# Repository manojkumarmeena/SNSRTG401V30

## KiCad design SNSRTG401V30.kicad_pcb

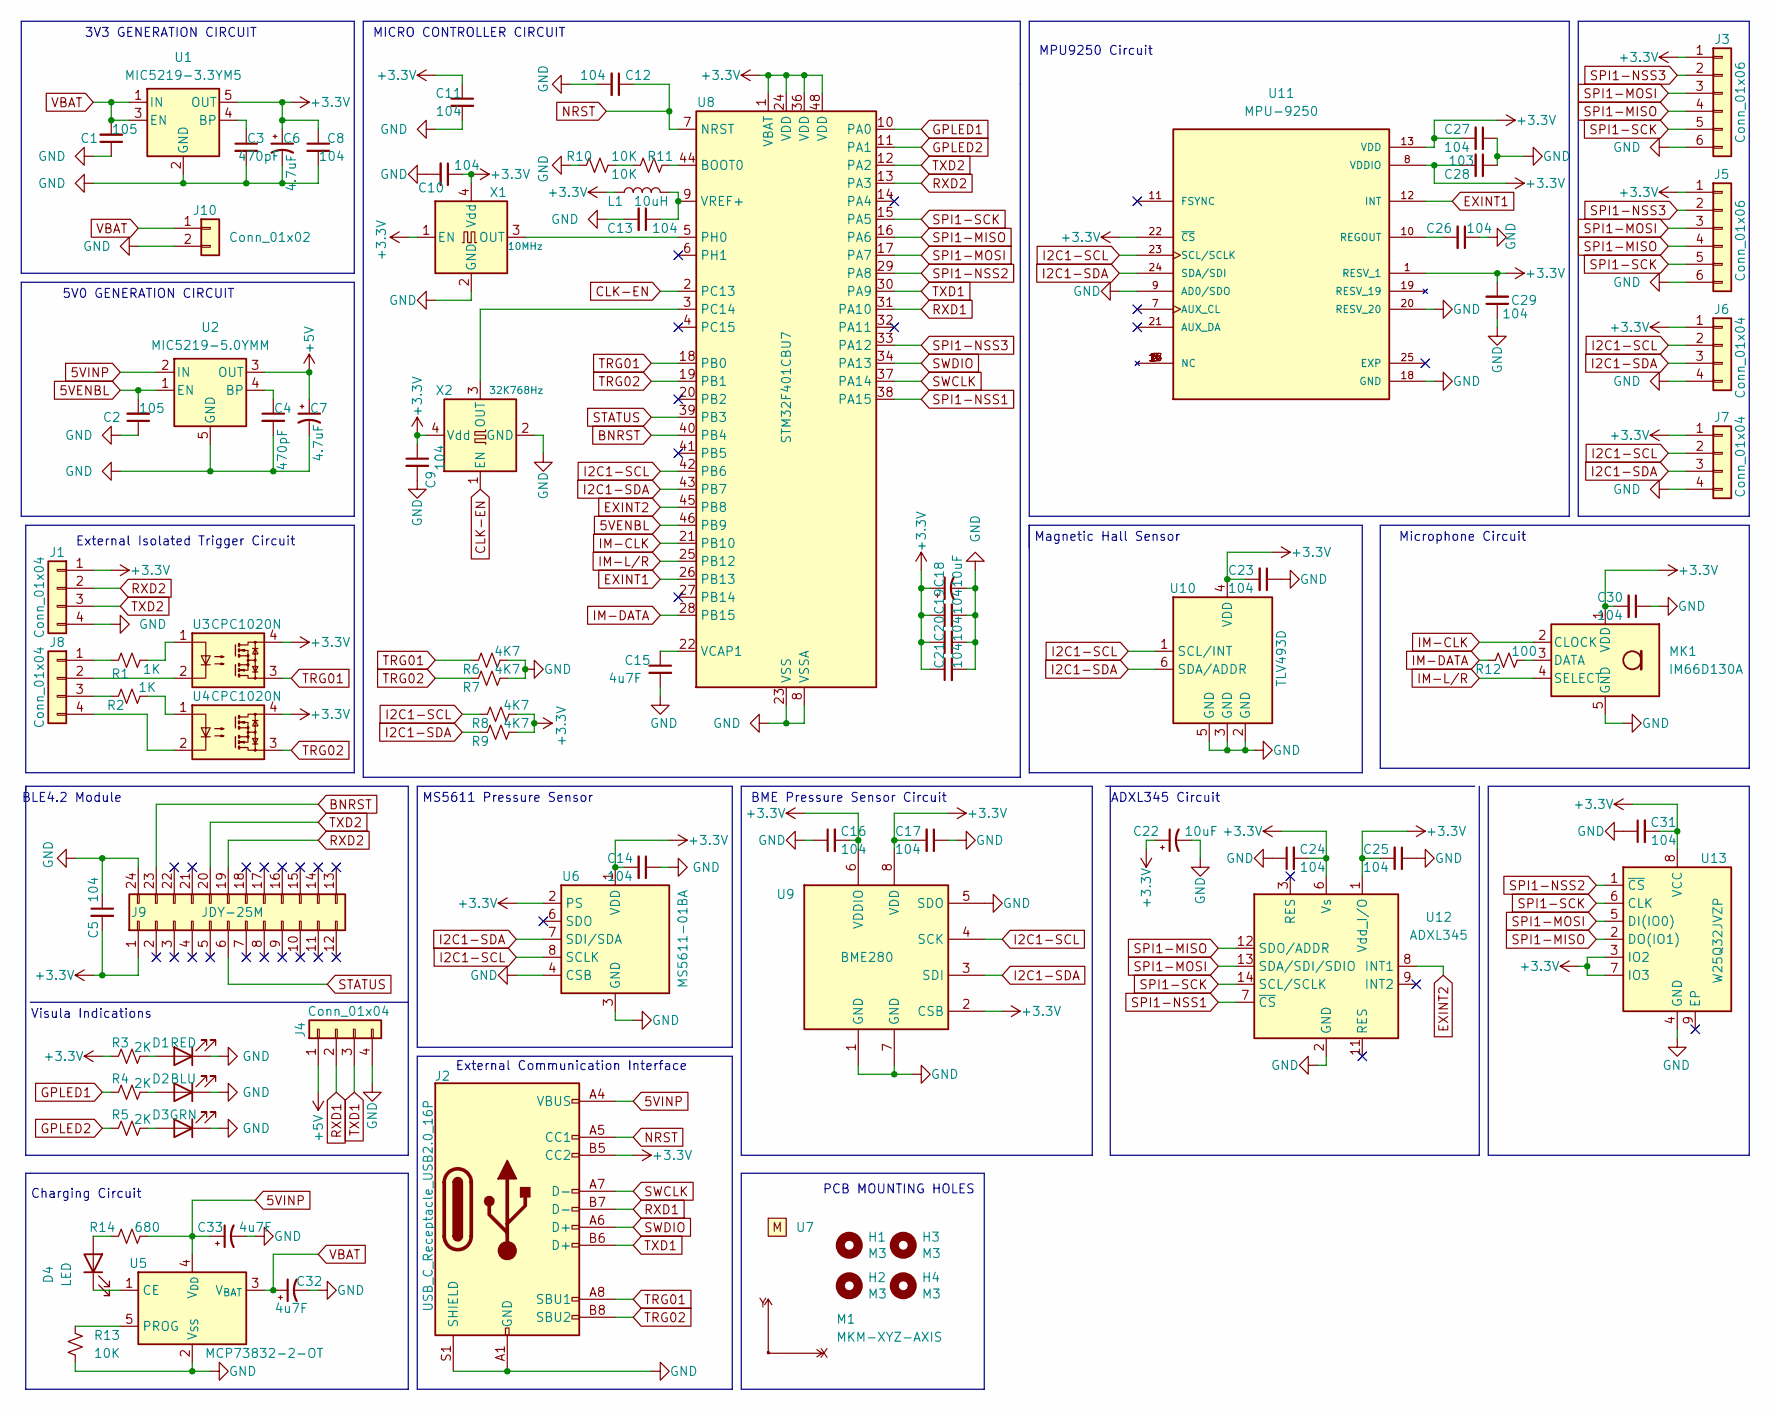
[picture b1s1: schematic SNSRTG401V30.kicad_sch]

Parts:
C1, C2: 105; C_0805_2012Metric_Pad1.18x1.45mm_HandSolder; PartNo C0805C105K4RACAUTO
C3, C4: 470pF; C_0603_1608Metric_Pad1.08x0.95mm_HandSolder; PartNo C0603C471J5GACAUTO
C5, C8, C9, C10, C11, C12, C13, C14, C16, C17, C19, C20, C21, C23, C24, C25, C26, C27, C29, C30, C31: 104; C_0603_1608Metric_Pad1.08x0.95mm_HandSolder; PartNo C0603C104J5RACAUTO
C6, C7: 4.7uF; CP_EIA-3216-18_Kemet-A; PartNo T491A475K016AT
C15: 4u7F; C_1206_3216Metric_Pad1.33x1.80mm_HandSolder; PartNo C1206C475K5PACTU
C18, C22: 10uF; CP_EIA-3216-18_Kemet-A; PartNo T491A106K016AT
C28: 103; C_0603_1608Metric_Pad1.08x0.95mm_HandSolder; PartNo C0603C103J3GECAUTO
C32, C33: 4u7F; CP_EIA-3216-18_Kemet-A
D1: RED; LED_0603_1608Metric_Pad1.05x0.95mm_HandSolder; PartNo VLMS1300-GS08
D2: BLU; LED_0603_1608Metric_Pad1.05x0.95mm_HandSolder; PartNo VLMB1300-GS08
D3: GRN; LED_0603_1608Metric_Pad1.05x0.95mm_HandSolder; PartNo VLMTG1401-GS08
D4: LED; LED_0603_1608Metric_Pad1.05x0.95mm_HandSolder
H1, H2, H3, H4: M3; MountingHole_3.2mm_M3
J1, J4, J6, J8: Conn_01x04; PinHeader_1x04_P1.27mm_Vertical
J2: USB_C_Receptacle_USB2.0_16P; USB_C_Receptacle_GCT_USB4105-xx-A_16P_TopMnt_Horizontal
J3: Conn_01x06; PinHeader_1x06_P1.27mm_Vertical
J5: Conn_01x06; PinHeader_1x06_P1.00mm_Vertical
J7: Conn_01x04; PinHeader_1x04_P1.00mm_Vertical
J9: JDY-25M; JDY-08
J10: Conn_01x02; PinHeader_1x02_P1.27mm_Vertical
L1: 10uH; L_0603_1608Metric_Pad1.05x0.95mm_HandSolder; PartNo FCM1608KF-601T03
M1: MKM-XYZ-AXIS; BullsEye
MK1: IM66D130A; Infineon_PG-LLGA-5-1
R1, R2: 1K; R_0603_1608Metric_Pad0.98x0.95mm_HandSolder; PartNo CRCW06031K00FKEAHP
R3, R4, R5: 2K; R_0603_1608Metric_Pad0.98x0.95mm_HandSolder; PartNo CRCW06032K00FKEAHP
R6, R7, R8, R9: 4K7; R_0603_1608Metric_Pad0.98x0.95mm_HandSolder; PartNo CRCW06034K70FKEAHP
R10, R11: 10K; R_0603_1608Metric_Pad0.98x0.95mm_HandSolder; PartNo CRCW060310K0FKEAHP
R12: 100; R_0603_1608Metric_Pad0.98x0.95mm_HandSolder; PartNo CRCW0603120RFKEAHP
R13: 10K; R_0603_1608Metric_Pad0.98x0.95mm_HandSolder
R14: 680; R_0603_1608Metric_Pad0.98x0.95mm_HandSolder
U1: MIC5219-3.3YM5; SOT-23-5; PartNo MIC5219-3.3YM5-TR
U2: MIC5219-5.0YMM; MSOP-8_3x3mm_P0.65mm; PartNo MIC5219-5.0YMM
U3, U4: CPC1020N; SOP-4_3.8x4.1mm_P2.54mm; PartNo CPC1020N
U5: MCP73832-2-OT; SOT-23-5
U6: MS5611-01BA; LGA-8_3x5mm_P1.25mm; PartNo MS561101BA03-50
U7: MKM-LOGON-V10; MKMLOGO-P
U8: STM32F401CBU7; QFN-48-1EP_7x7mm_P0.5mm_EP5.6x5.6mm; PartNo STM32F401CBU7
U9: BME280; Bosch_LGA-8_2.5x2.5mm_P0.65mm_ClockwisePinNumbering; PartNo BME280
U10: TLV493D; SOT-23-6; PartNo TLV493DA1B6HTSA2
U11: MPU-9250; MPU9250-QFN24-3x3mm-P0.4mm; PartNo MPU-9250
U12: ADXL345; ADXL375-LGA-3x5MM; PartNo ADXL345BCCZ
U13: W25Q32JVZP; WSON-8-1EP_8x6mm_P1.27mm_EP3.4x4.3mm; PartNo W25Q512JVEIQ
X1: 10MHz; Oscillator_SMD_Abracon_ASDMB-4Pin_2.5x2.0mm; PartNo 8NJ-10.000MDE-T
X2: 32K768Hz; Oscillator_SMD_Abracon_ASDMB-4Pin_2.5x2.0mm; PartNo ABS07-120-32.768KHZ-T

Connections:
5VENBL: C2.2, U2.1 (EN), U8.46 (PB9)
5VINP: C33.1, J2.A4 (VBUS), J2.A9 (VBUS), J2.B4 (VBUS), J2.B9 (VBUS), R14.1, U2.2 (IN), U5.4 (V_{DD})
+3.3V: C5.2, C6.1, C8.1, C9.1, C10.1, C11.1, C14.2, C16.2, C17.2, C18.1, C19.1, C20.1, C21.1, C22.1, C23.2, C24.2, C25.2, C27.2, C28.2, C29.2, C30.2, C31.2, J1.1, J2.B5 (CC2), J3.1, J5.1, J6.1, J7.1, J9.1, L1.1, MK1.1 (VDD), R3.1, R8.2, R9.2, U1.5 (OUT), U3.4, U4.4, U6.1 (VDD), U6.2 (PS), U8.1 (VBAT), U8.24 (VDD), U8.36 (VDD), U8.48 (VDD), U9.2 (CSB), U9.6 (VDDIO), U9.8 (VDD), U10.4 (VDD), U11.1 (RESV_1), U11.8 (VDDIO), U11.13 (VDD), U11.22 (~CS), U12.1 (Vdd_I/O), U12.6 (Vs), U13.3 (IO2), U13.7 (IO3), U13.8 (VCC), X1.1 (EN), X1.4 (Vdd), X2.4 (Vdd)
+5V: C7.1, J4.1, U2.3 (OUT)
BNRST: J9.23, U8.40 (PB4)
CLK-EN: U8.2 (PC13), X2.1 (EN)
EXINT1: U8.26 (PB13), U11.12 (INT)
EXINT2: U8.45 (PB8), U12.8 (INT1)
GND: C1.1, C2.1, C3.2, C4.2, C5.1, C6.2, C7.2, C8.2, C9.2, C10.2, C11.2, C12.2, C13.2, C14.1, C15.2, C16.1, C17.1, C18.2, C19.2, C20.2, C21.2, C22.2, C23.1, C24.1, C25.1, C26.1, C27.1, C28.1, C29.1, C30.1, C31.1, C32.2, C33.2, D1.1 (K), D2.1 (K), D3.1 (K), J1.4, J2.A1 (GND), J2.A12 (GND), J2.B1 (GND), J2.B12 (GND), J2.S1 (SHIELD), J3.6, J4.4, J5.6, J6.4, J7.4, J9.24, J10.2, MK1.5 (GND), R6.2, R7.2, R10.1, R13.2, U1.2 (GND), U2.5 (GND), U2.6 (GND), U2.7 (GND), U2.8 (GND), U5.2 (V_{SS}), U6.3 (GND), U6.4 (CSB), U6.5 (CSB), U8.8 (VSSA), U8.23 (VSS), U8.35 (VSS), U8.47 (VSS), U8.49 (VSS), U9.1 (GND), U9.5 (SDO), U9.7 (GND), U10.2 (GND), U10.3 (GND), U10.5 (GND), U11.9 (AD0/SDO), U11.18 (GND), U11.20 (RESV_20), U12.2 (GND), U12.4 (GND), U12.5 (GND), U13.4 (GND), X1.2 (GND), X2.2 (GND)
GPLED1: R4.1, U8.10 (PA0)
GPLED2: R5.1, U8.11 (PA1)
I2C1-SCL: J6.2, J7.2, R8.1, U6.8 (SCLK), U8.42 (PB6), U9.4 (SCK), U10.1 (SCL/INT), U11.23 (SCL/SCLK)
I2C1-SDA: J6.3, J7.3, R9.1, U6.7 (SDI/SDA), U8.43 (PB7), U9.3 (SDI), U10.6 (SDA/ADDR), U11.24 (SDA/SDI)
IM-CLK: MK1.2 (CLOCK), U8.21 (PB10)
IM-DATA: R12.1, U8.28 (PB15)
IM-L/R: MK1.4 (SELECT), U8.25 (PB12)
NRST: C12.1, J2.A5 (CC1), U8.7 (NRST)
unnamed: D1.2 (A), R3.2
unnamed: D2.2 (A), R4.2
unnamed: D3.2 (A), R5.2
unnamed: D4.2 (A), R14.2
unnamed: D4.1 (K), U5.1 (CE)
unnamed: J8.1, R1.1
unnamed: J8.2, U3.2
unnamed: J8.3, R2.1
unnamed: J8.4, U4.2
unnamed: MK1.3 (DATA), R12.2
unnamed: R1.2, U3.1
unnamed: R2.2, U4.1
unnamed: R10.2, R11.1
unnamed: C3.1, U1.4 (BP)
unnamed: C4.1, U2.4 (BP)
unnamed: R13.1, U5.5 (PROG)
unnamed: R11.2, U8.44 (BOOT0)
unnamed: U8.3 (PC14), X2.3 (OUT)
unnamed: U8.5 (PH0), X1.3 (OUT)
unnamed: C15.1, U8.22 (VCAP1)
unnamed: C13.1, L1.2, U8.9 (VREF+)
unnamed: C26.2, U11.10 (REGOUT)
RXD1: J2.B7 (D-), J4.2, U8.31 (PA10)
RXD2: J1.2, J9.19, U8.13 (PA3)
SPI1-MISO: J3.4, J5.4, U8.16 (PA6), U12.12 (SDO/ADDR), U13.2 (DO(IO1))
SPI1-MOSI: J3.3, J5.3, U8.17 (PA7), U12.13 (SDA/SDI/SDIO), U13.5 (DI(IO0))
SPI1-NSS1: U8.38 (PA15), U12.7 (~CS)
SPI1-NSS2: U8.29 (PA8), U13.1 (~CS)
SPI1-NSS3: J3.2, J5.2, U8.33 (PA12)
SPI1-SCK: J3.5, J5.5, U8.15 (PA5), U12.14 (SCL/SCLK), U13.6 (CLK)
STATUS: J9.6, U8.39 (PB3)
SWCLK: J2.A7 (D-), U8.37 (PA14)
SWDIO: J2.A6 (D+), U8.34 (PA13)
TRG01: J2.A8 (SBU1), R6.1, U3.3, U8.18 (PB0)
TRG02: J2.B8 (SBU2), R7.1, U4.3, U8.19 (PB1)
TXD1: J2.B6 (D+), J4.3, U8.30 (PA9)
TXD2: J1.3, J9.20, U8.12 (PA2)
VBAT: C1.2, C32.1, J10.1, U1.1 (IN), U1.3 (EN), U5.3 (V_{BAT})

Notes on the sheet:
Magnetic Hall Sensor
External Isolated Trigger Circuit
External Communication Interface
Charging Circuit
BME Pressure Sensor Circuit
PCB MOUNTING HOLES
Visula Indications
MICRO CONTROLLER CIRCUIT
BLE4.2 Module
ADXL345 Circuit
3V3 GENERATION CIRCUIT
5V0 GENERATION CIRCUIT
Microphone Circuit
MPU9250 Circuit
MS5611 Pressure Sensor

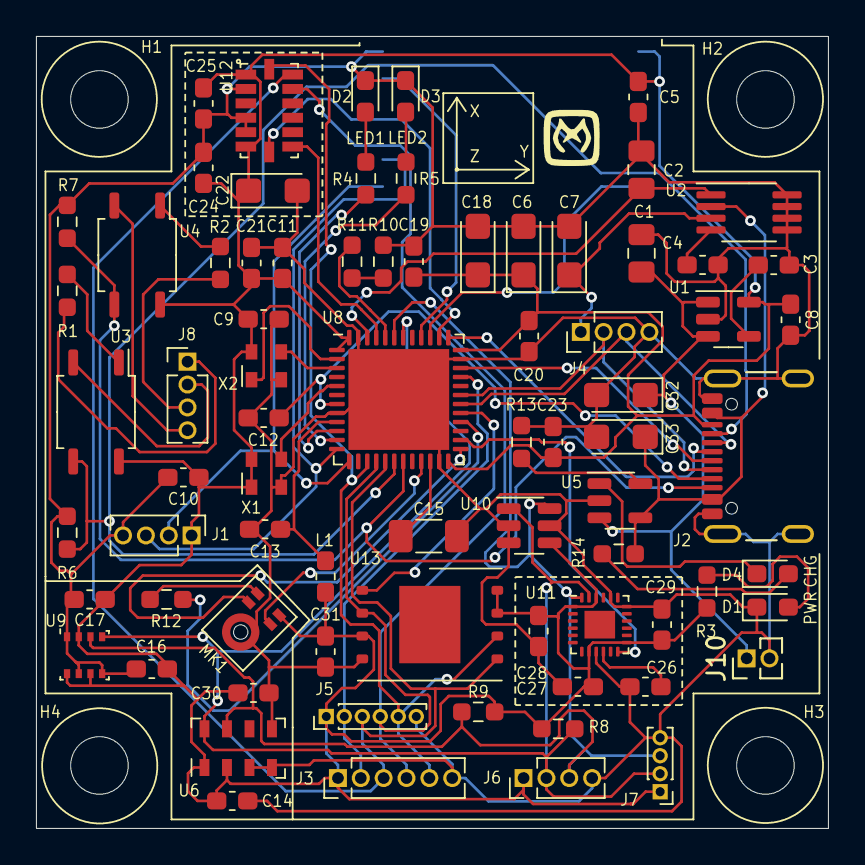
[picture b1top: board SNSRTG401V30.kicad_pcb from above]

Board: 2 copper layers, 44.0 x 44.0 mm, 83 parts (1 on the bottom side), 55 nets.

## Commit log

2024-11-30 Base Version Uploaded.
2024-11-30 Plot Files Updated
2024-12-05 new Gerber generaated
2024-12-11 DFM Issue of Lion Circuits Resolved.
